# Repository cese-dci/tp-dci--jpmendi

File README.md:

# tp-dci--jpmendi
tp-dci--jpmendi created by GitHub Classroom

ARCHIVOS DEL TPFINAL DE DISEÑO DE PCB

El presente modulo es un control de motor de continua mediante de relay, con sensor de corriente,
para detener el mismo segun determinado torque, utilizando para ello un dip switch donde se pueden
activar distintas resistencias como referencias para que un PIC active o desactive los releay (uno para cada lado y 
un tercer relay que es para activar o desactivar la placa)

Posee dos entradas para los interruptores que estan fuera de la placa. y dos salidas a los motores

UN DETALLE: Requiere agregar ciertas pistas a la mascara antisoldante para para poder estañarlas luego de terminado el PCB

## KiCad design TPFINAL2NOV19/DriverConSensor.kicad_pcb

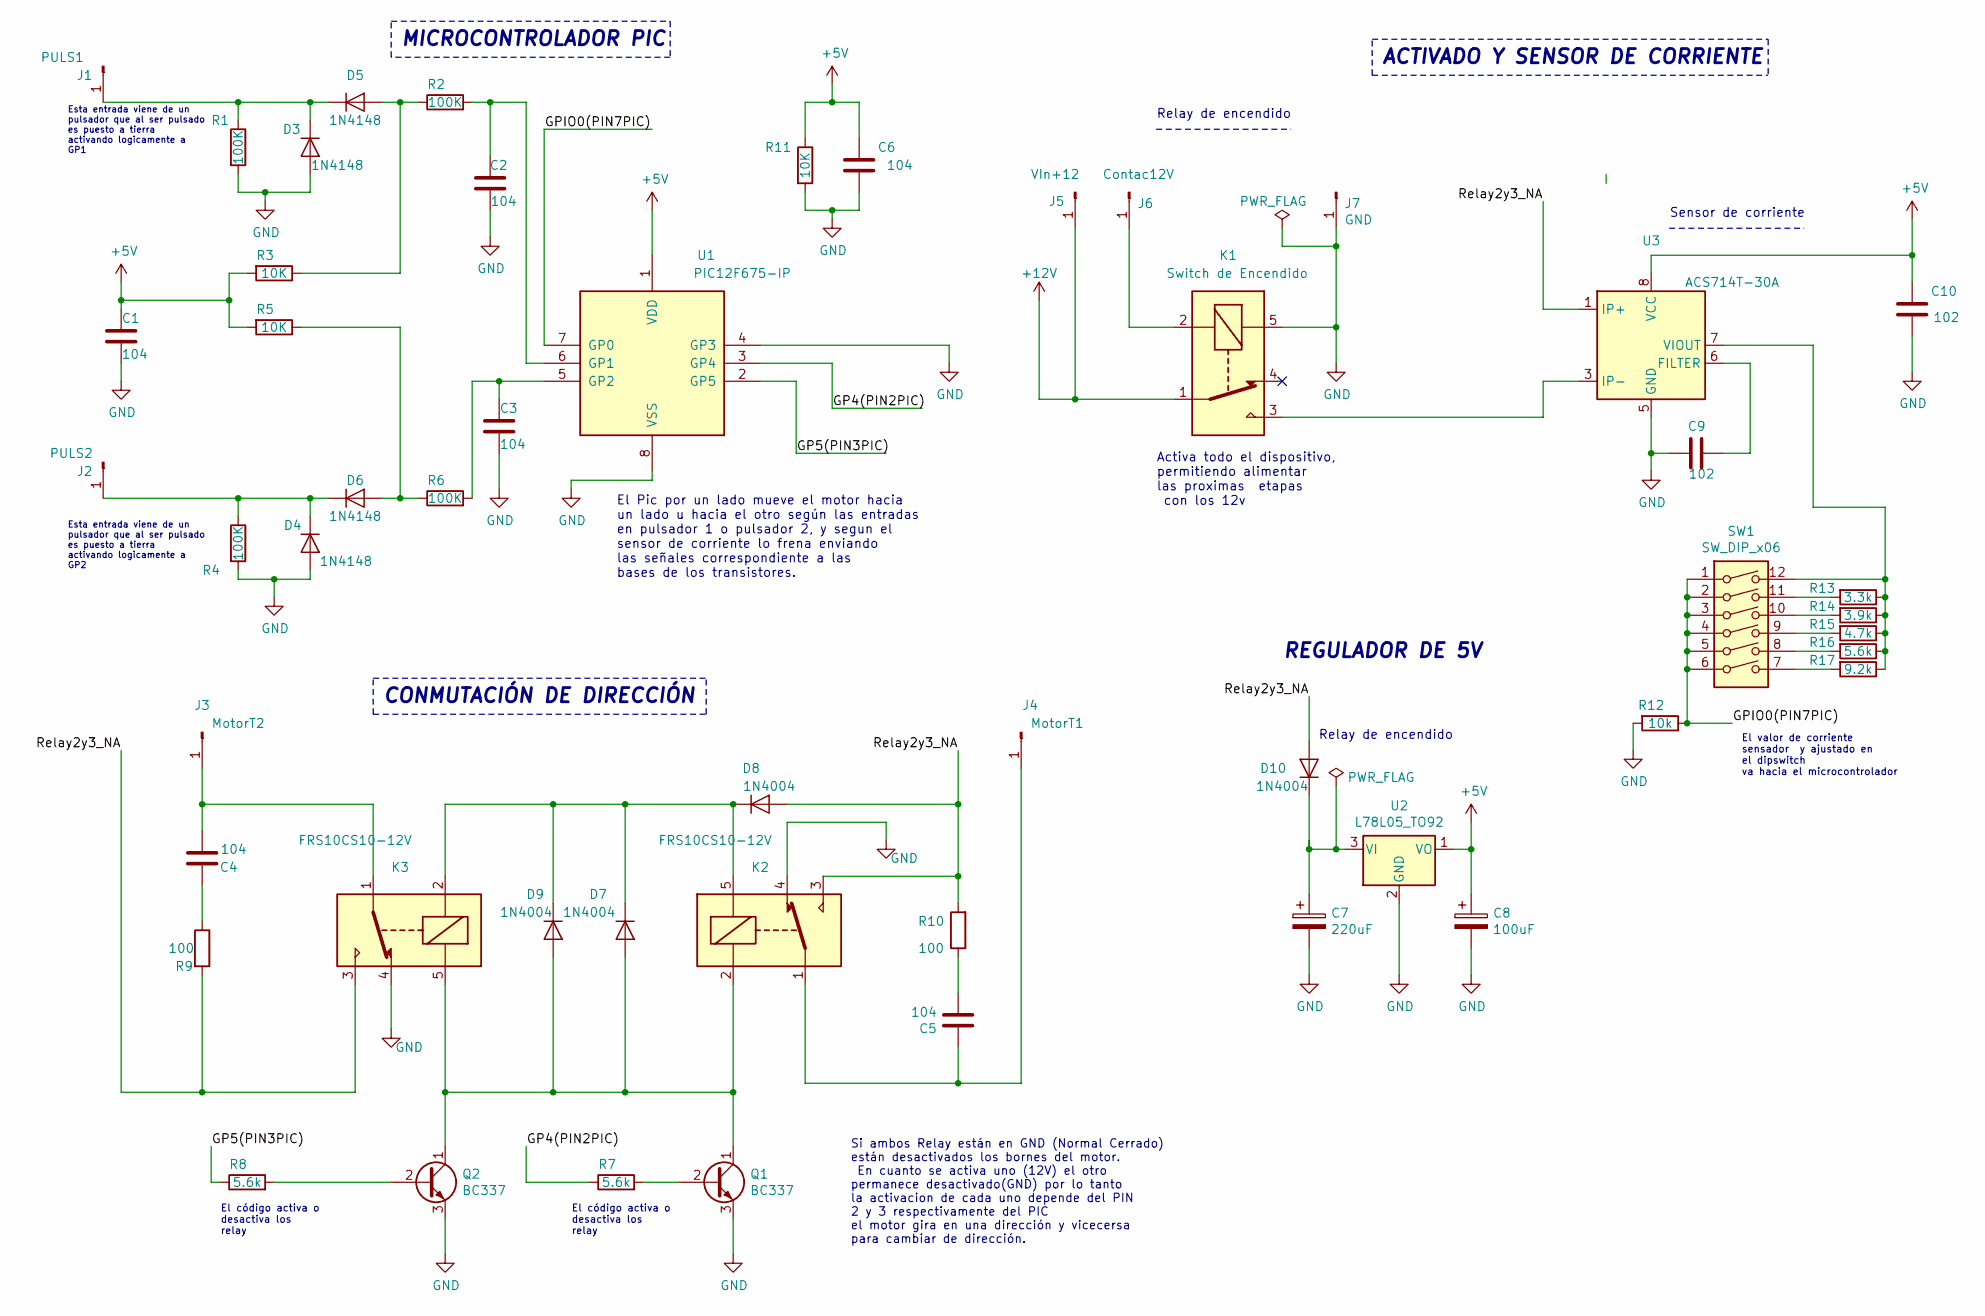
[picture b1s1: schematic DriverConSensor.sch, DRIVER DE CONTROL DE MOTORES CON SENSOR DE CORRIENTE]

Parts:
C1, C2, C4, C5: 104; C_Disc_D3.8mm_W2.6mm_P2.50mm
C3, C6: 104; C_Disc_D5.0mm_W2.5mm_P5.00mm
C7: 220uF; C_Radial_D6.3mm_H11.0mm_P2.50mm
C8: 100uF; C_Radial_D6.3mm_H11.0mm_P2.50mm
C9: 102; C_Disc_D5.0mm_W2.5mm_P5.00mm
C10: 102; C_Disc_D3.8mm_W2.6mm_P2.50mm
D3, D4, D5, D6: 1N4148; D_DO-35_SOD27_P7.62mm_Horizontal
D7, D8, D9, D10: 1N4004; D_DO-41_SOD81_P10.16mm_Horizontal
J1: PULS1; SolderWirePad_1x01_Drill1.2mm
J2: PULS2; SolderWirePad_1x01_Drill1.2mm
J3: MotorT2; SolderWirePad_1x01_Drill2mm
J4: MotorT1; SolderWirePad_1x01_Drill2mm
J5: VIn+12; SolderWirePad_1x01_Drill2mm
J6: Contac12V; SolderWirePad_1x01_Drill1.2mm
J7: GND; SolderWirePad_1x01_Drill2mm
K1: Switch de Encendido; Relay_SPDT_Omron-G5LE-1
K2, K3: FRS10CS10-12V; Relay_SPDT_Omron-G5LE-1
Q1, Q2: BC337; TO-92_Inline_Wide
R1, R2, R4, R6: 100K; R_Axial_DIN0204_L3.6mm_D1.6mm_P7.62mm_Horizontal
R3, R5, R11: 10K; R_Axial_DIN0204_L3.6mm_D1.6mm_P7.62mm_Horizontal
R7, R8, R16: 5.6k; R_Axial_DIN0204_L3.6mm_D1.6mm_P7.62mm_Horizontal
R9, R10: 100; R_Axial_DIN0204_L3.6mm_D1.6mm_P7.62mm_Horizontal
R12: 10k; R_Axial_DIN0204_L3.6mm_D1.6mm_P7.62mm_Horizontal
R13: 3.3k; R_Axial_DIN0204_L3.6mm_D1.6mm_P7.62mm_Horizontal
R14: 3.9k; R_Axial_DIN0204_L3.6mm_D1.6mm_P7.62mm_Horizontal
R15: 4.7k; R_Axial_DIN0204_L3.6mm_D1.6mm_P7.62mm_Horizontal
R17: 9.2k; R_Axial_DIN0204_L3.6mm_D1.6mm_P7.62mm_Horizontal
SW1: SW_DIP_x06; SW_DIP_SPSTx06_Slide_6.7x16.8mm_W7.62mm_P2.54mm_LowProfile
U1: PIC12F675-IP; DIP-8_W7.62mm
U2: L78L05_TO92; TO-92_Inline
U3: ACS714T-30A; SOIC-8_3.9x4.9mm_P1.27mm

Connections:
+5V: C1.1, C6.1, C8.1, C10.1, R3.2, R5.2, R11.1, U1.1 (VDD), U2.1 (VO), U3.8 (VCC)
+12V: J5.1, K1.1
/GP4(PIN2PIC): R7.1, U1.3 (GP4)
/GP5(PIN3PIC): R8.1, U1.2 (GP5)
/GPIO0(PIN7PIC): R12.1, SW1.1, SW1.2, SW1.3, SW1.4, SW1.5, SW1.6, U1.7 (GP0)
/Relay2y3_NA: D8.2 (A), D10.2 (A), K2.3, K3.3, R9.2, R10.2, U3.1 (IP+), U3.2 (IP+)
GND: C1.2, C2.1, C3.2, C6.2, C7.2, C8.2, C9.2, C10.2, D3.2 (A), D4.2 (A), J7.1, K1.5, K2.4, K3.4, Q1.3 (E), Q2.3 (E), R1.2, R4.2, R11.2, R12.2, U1.4 (GP3), U1.8 (VSS), U2.2 (GND), U3.5 (GND)
unnamed: C2.2, R2.2, U1.6 (GP1)
unnamed: C3.1, R6.2, U1.5 (GP2)
unnamed: C4.1, R9.1
unnamed: C4.2, J3.1, K3.1
unnamed: C5.1, J4.1, K2.1
unnamed: C5.2, R10.1
unnamed: C7.1, D10.1 (K), U2.3 (VI)
unnamed: C9.1, U3.6 (FILTER)
unnamed: D3.1 (K), D5.1 (K), J1.1, R1.1
unnamed: D4.1 (K), D6.1 (K), J2.1, R4.1
unnamed: D5.2 (A), R2.1, R3.1
unnamed: D6.2 (A), R5.1, R6.1
unnamed: D7.1 (K), D8.1 (K), D9.1 (K), K2.5, K3.2
unnamed: D7.2 (A), D9.2 (A), K2.2, K3.5, Q1.1 (C), Q2.1 (C)
unnamed: J6.1, K1.2
unnamed: K1.3, U3.3 (IP-), U3.4 (IP-)
unnamed: Q1.2 (B), R7.2
unnamed: Q2.2 (B), R8.2
unnamed 26: R13.1, R14.1, R15.1, R16.1, R17.1, SW1.12, U3.7 (VIOUT); also elsewhere on the board
unnamed: R13.2, SW1.11
unnamed: R14.2, SW1.10
unnamed: R15.2, SW1.9
unnamed: R16.2, SW1.8
unnamed: R17.2, SW1.7

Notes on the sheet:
El valor de corriente sensador y ajustado en el dipswitch va hacia el microcontrolador
Sensor de corriente
MICROCONTROLADOR PIC
Relay de encendido
Activa todo el dispositivo, permitiendo alimentar las proximas etapas con los 12v
El Pic por un lado mueve el motor hacia un lado u hacia el otro según las entradas en pulsador 1 o pulsador 2, y segun el sensor de corriente lo frena enviando las señales correspondiente a las bases de los transistores.
Esta entrada viene de un pulsador que al ser pulsado es puesto a tierra activando logicamente a GP2
Esta entrada viene de un pulsador que al ser pulsado es puesto a tierra activando logicamente a GP1
Si ambos Relay están en GND (Normal Cerrado) están desactivados los bornes del motor. En cuanto se activa uno (12V) el otro permanece desactivado(GND) por lo tanto la activacion de cada uno depende del PIN 2 y 3 respectivamente del PIC el motor gira en una dirección y vicecersa para cambiar de dire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
El código activa o desactiva los relay
CONMUTACIÓN DE DIRECCIÓN
ACTIVADO Y SENSOR DE CORRIENTE
REGULADOR DE 5V

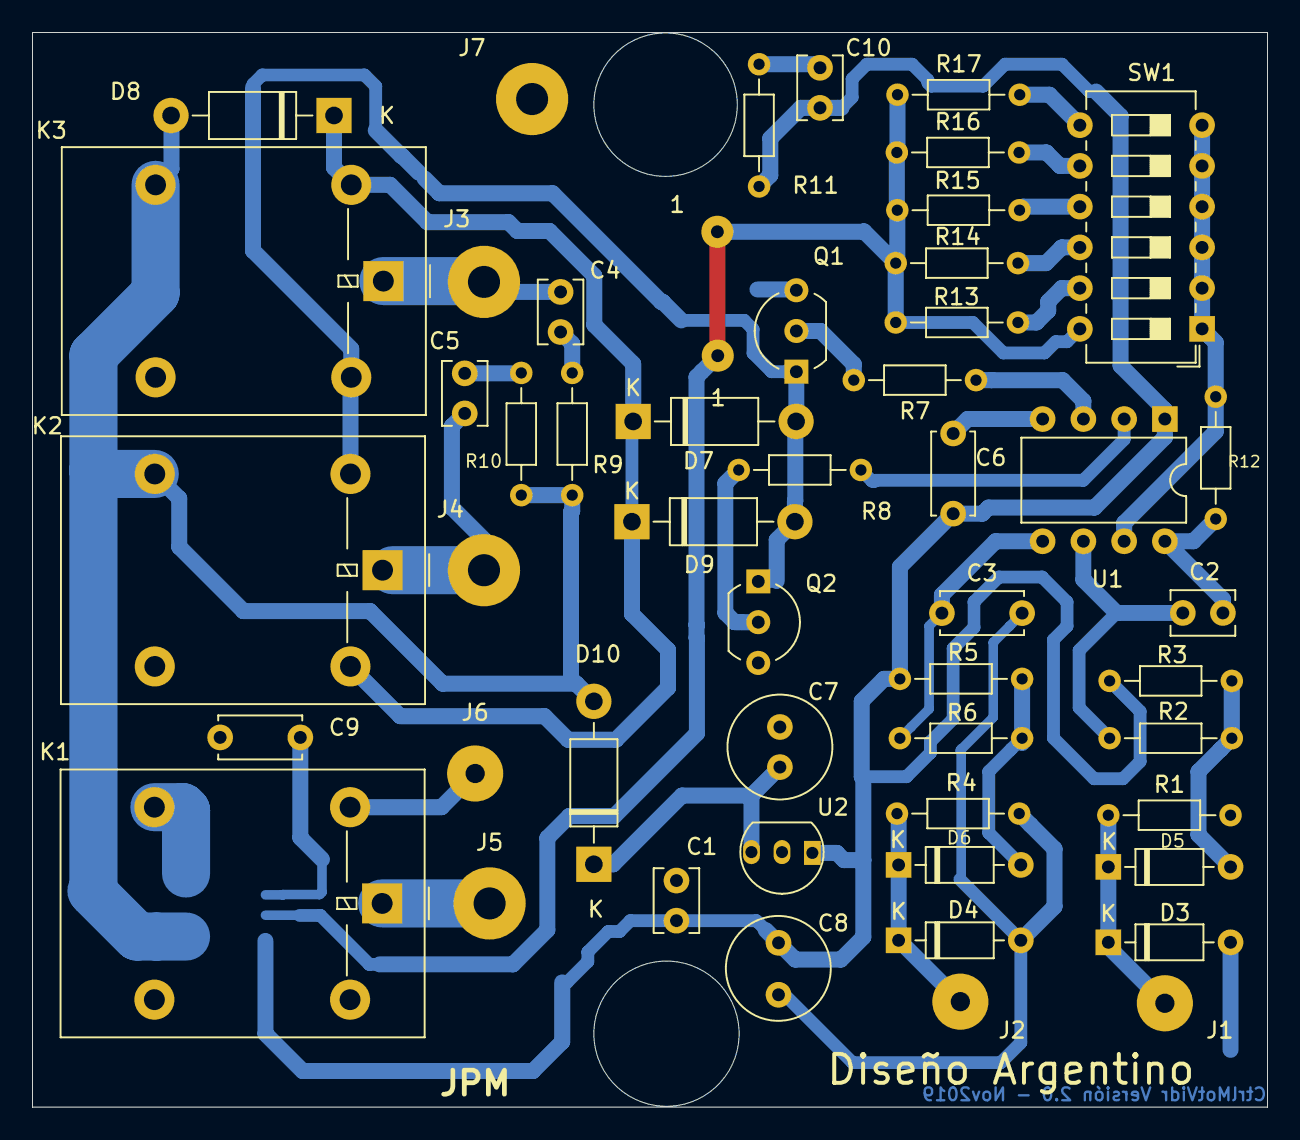
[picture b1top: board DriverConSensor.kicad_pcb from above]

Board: 2 copper layers, 77.0 x 67.0 mm, 53 parts (1 on the bottom side), 31 nets.

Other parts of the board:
1, 1#2: SolderWirePad_1x01_Drill0.8mm

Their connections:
unnamed 26: 1.2, 1#2.1; also elsewhere on the board

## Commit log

2019-10-01 esquematico
2019-11-02 actual
2019-11-02 actual2
2019-11-02 actual3
2019-11-02 actual4
2019-11-03 actual5
2019-11-03 actual6
2019-11-03 actual7
2019-11-03 PCB_casi_listo
2019-11-04 PCB_casi_listo2
2019-11-05 PCB_casi_listo3
2019-11-05 PCB_casi_listo4
2019-11-05 PCB_casi_listo5
2019-11-15 PCB_Final
